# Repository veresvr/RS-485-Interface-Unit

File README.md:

# RS-485 Interface Unit

##### This module is simple isolated RS-485 -> UART converter, which designed to be part of CNC control box. CNC itself you may see here [Laser CNC].

</img>

[Laser CNC]: <https://github.com/veresvr/LaserCNCMachine>

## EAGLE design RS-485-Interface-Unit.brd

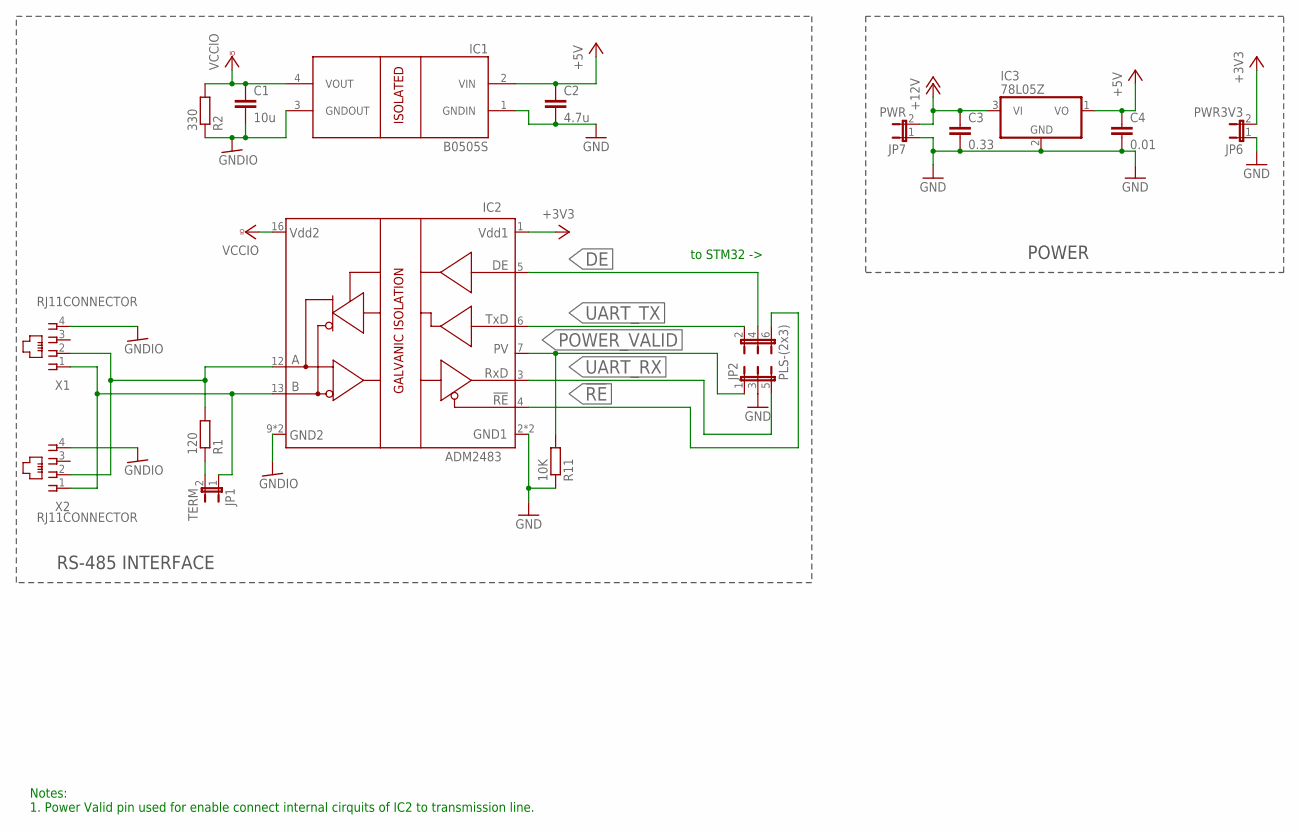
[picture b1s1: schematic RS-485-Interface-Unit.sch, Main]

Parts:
C1: 10u; C0805
C2: 4.7u; C0805
C3: 0.33; C2012
C4: 0.01; C2012
IC1: B0505S; SC_PACKAGE
IC2: ADM2483; SO16W
IC3: 78L05Z; TO92
JP1: TERM; JP1
JP2: PLS-(2х3)
JP6: PWR3V3; JP1
JP7: PWR; JP1
R1: 120; 0204/7
R2: 330; R0805
R11: 10K; R0805
X1, X2: RJ11CONNECTOR; RJ11_NONAME

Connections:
!RE: IC2.4 (!RE), JP2.6
+3V3: IC2.1 (VDD1), JP6.2
+5V: C2.1, C4.1, IC1.2 (VIN), IC3.1 (VO)
+12V: C3.1, IC3.3 (VI), JP7.2
A-IN: IC2.12 (A), R1.2, X1.2, X2.2
B-IN: IC2.13 (B), JP1.1, X1.1, X2.1
DE: IC2.5 (DE), JP2.4
GND: C2.2, C3.2, C4.2, IC1.1 (GNDIN), IC2.2 (GND1), IC2.8 (GND1), IC3.2 (GND), JP2.3, JP6.1, JP7.1, R11.1
GNDIO: C1.2, IC1.3 (GNDOUT), IC2.9 (GND2), IC2.15 (GND2), R2.1, X1.4, X2.4
unnamed: JP1.2, R1.1
POWER_VALID: IC2.7 (PV), JP2.1, R11.2
UART_RX: IC2.3 (RXD), JP2.5
UART_TX: IC2.6 (TXD), JP2.2
VCCIO: C1.1, IC1.4 (VOUT), IC2.16 (VDD2), R2.2

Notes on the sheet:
RS-485 INTERFACE
POWER
to STM32 ->
Notes: 1. Power Valid pin used for enable connect internal cirquits of IC2 to transmission line.

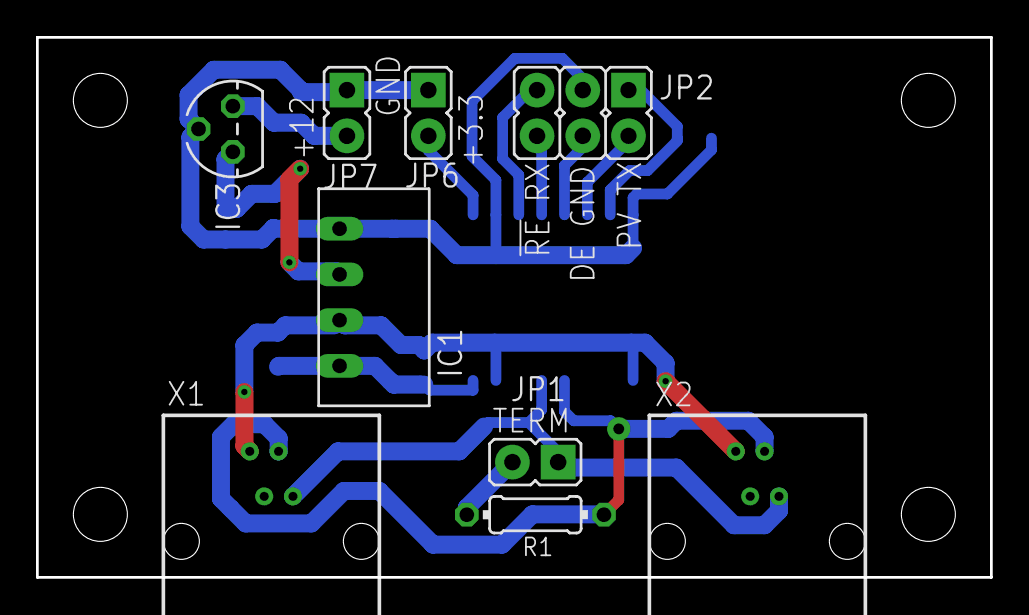
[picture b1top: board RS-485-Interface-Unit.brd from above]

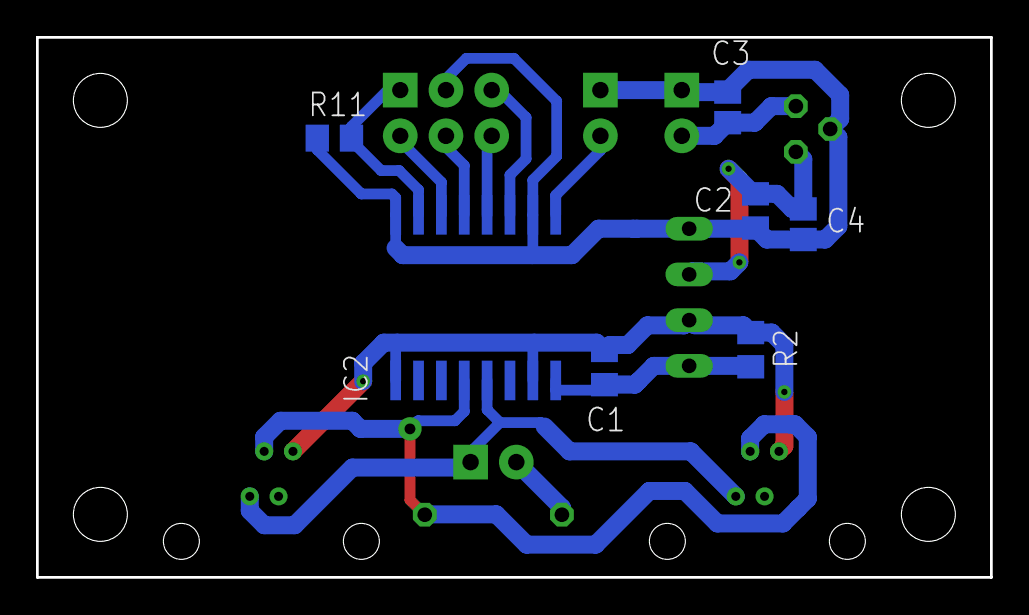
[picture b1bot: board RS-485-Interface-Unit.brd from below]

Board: 2 copper layers, 53.0 x 30.0 mm, 16 parts (7 on the bottom side), 14 nets.

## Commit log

2021-03-06 Added scheme and pcb
2021-03-06 Updated pcb
2021-03-07 Board tracing done
2021-03-08 Added 3D model
2021-06-13 Bugfix: added local GND to the RJ connector
2021-06-14 Updated the readme
2021-06-15 A little updates
